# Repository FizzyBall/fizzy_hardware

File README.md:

# Hardware
Embodiment of the robotic ball

<!-- 

Drivetrain V3.0

Drivetrain V3.1

Rigid shell V1

Rigid shell V2

Flexible shell V1

Flexible shell V2
 -->

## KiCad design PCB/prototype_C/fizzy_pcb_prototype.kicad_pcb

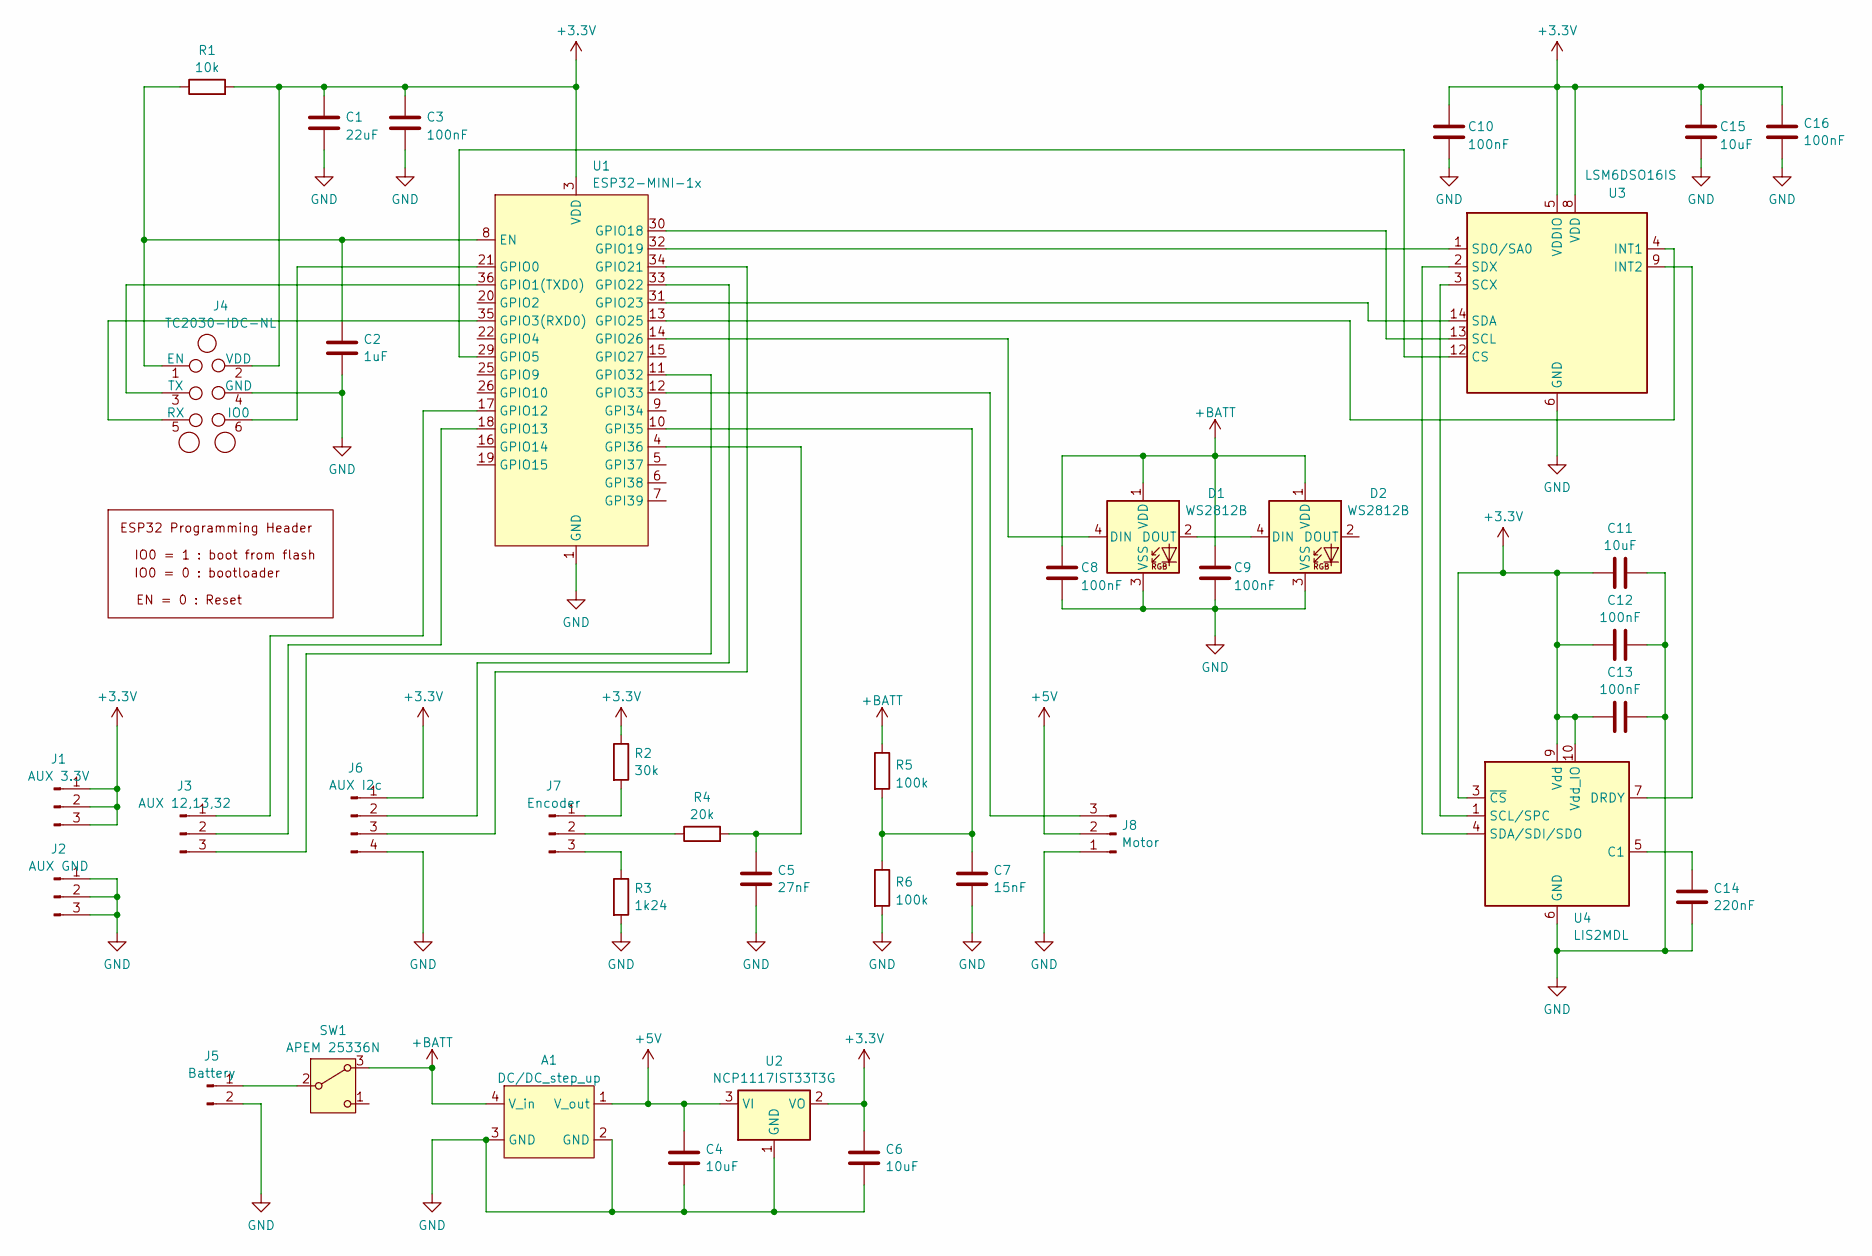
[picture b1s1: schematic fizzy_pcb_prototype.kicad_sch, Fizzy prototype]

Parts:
A1: DC/DC_step_up; DCDC+BAT
C1: 22uF; C_0805_2012Metric
C2: 1uF; C_0603_1608Metric
C3, C8, C9, C10, C12, C13, C16: 100nF; C_0603_1608Metric
C4, C6, C11, C15: 10uF; C_0805_2012Metric
C5: 27nF; C_0603_1608Metric
C7: 15nF; C_0603_1608Metric
C14: 220nF; C_0805_2012Metric
D1, D2: WS2812B; LED_WS2812B_PLCC4_5.0x5.0mm_P3.2mm
J1: AUX 3.3V; PinHeader_1x03_P2.54mm_Vertical
J2: AUX GND; PinHeader_1x03_P2.54mm_Vertical
J3: AUX 12,13,32; PinHeader_1x03_P2.54mm_Vertical
J4: TC2030-IDC_ESP; Tag-Connect_TC2030-IDC-NL_2x03_P1.27mm_Vertical
J5: Battery; BatteryHolder_Keystone_1043_1x18650
J6: AUX I2c; PinHeader_1x04_P2.54mm_Vertical
J7: Encoder; JST_PH_B3B-PH-SM4-TB_1x03-1MP_P2.00mm_Vertical
J8: Motor; JST_PH_B3B-PH-SM4-TB_1x03-1MP_P2.00mm_Vertical
R1: 10k; R_0603_1608Metric
R2: 30k; R_0603_1608Metric
R3: 1k24; R_0603_1608Metric
R4: 20k; R_0603_1608Metric
R5, R6: 100k; R_0603_1608Metric
SW1: APEM 25336N; APEM_25336N
U1: ESP32-MINI-1x; ESP32-MINI-1
U2: NCP1117IST33T3G; SOT-223-3_TabPin2
U3: LSM6DSO16IS; LGA-14_3x2.5mm_P0.5mm_LayoutBorder3x4y
U4: LIS2MDL; LGA-12_2x2mm_P0.5mm

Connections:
+3.3V: C1.2, C3.2, C6.2, C10.2, C11.2, C12.2, C13.2, C15.2, C16.2, J1.1, J1.2, J1.3, J4.2 (VDD), J6.1, R1.2, R2.1, U1.3 (VDD), U2.2 (VO), U3.5 (VDDIO), U3.8 (VDD), U4.3 (~CS), U4.9 (Vdd), U4.10 (Vdd_IO)
+5V: A1.1 (V_out), C4.2, J8.2, U2.3 (VI)
+BATT: A1.4 (V_in), C8.2, C9.2, D1.1 (VDD), D2.1 (VDD), R5.1, SW1.3 (A)
GND: A1.2 (GND), A1.3 (GND), C1.1, C2.2, C3.1, C4.1, C5.1, C6.1, C7.1, C8.1, C9.1, C10.1, C11.1, C12.1, C13.1, C14.1, C15.1, C16.1, D1.3 (VSS), D2.3 (VSS), J2.1, J2.2, J2.3, J4.4 (GND), J5.2, J6.4, J8.1, R3.2, R6.2, U1.1 (GND), U1.2 (GND), U1.27 (GND), U1.38 (GND), U1.39 (GND), U1.40 (GND), U1.41 (GND), U1.42 (GND), U1.43 (GND), U1.44 (GND), U1.45 (GND), U1.46 (GND), U1.47 (GND), U1.48 (GND), U1.49 (GND), U1.50 (GND), U1.51 (GND), U1.52 (GND), U1.53 (GND), U1.54 (GND), U1.55 (GND), U2.1 (GND), U3.6 (GND), U3.7 (GND), U4.6 (GND), U4.8 (GND)
unnamed: D1.4 (DIN), U1.14 (GPIO26)
unnamed: D1.2 (DOUT), D2.4 (DIN)
unnamed: J3.1, U1.17 (GPIO12)
unnamed: J3.2, U1.18 (GPIO13)
unnamed: J3.3, U1.11 (GPIO32)
unnamed: C2.1, J4.1 (EN), R1.1, U1.8 (EN)
unnamed: J4.6 (IO0), U1.21 (GPIO0)
unnamed: J4.5 (RX), U1.35 (GPIO3(RXD0))
unnamed: J4.3 (TX), U1.36 (GPIO1(TXD0))
unnamed: J5.1, SW1.2 (B)
unnamed: J6.2, U1.33 (GPIO22)
unnamed: J6.3, U1.34 (GPIO21)
unnamed: J7.1, R2.2
unnamed: J7.2, R4.1
unnamed: J7.3, R3.1
unnamed: J8.3, U1.12 (GPIO33)
unnamed: C7.2, R5.2, R6.1, U1.10 (GPI35)
unnamed: C5.2, R4.2, U1.4 (GPI36)
unnamed: U1.29 (GPIO5), U3.12 (CS)
unnamed: U1.30 (GPIO18), U3.13 (SCL)
unnamed: U1.32 (GPIO19), U3.1 (SDO/SA0)
unnamed: U1.31 (GPIO23), U3.14 (SDA)
unnamed: U1.13 (GPIO25), U3.4 (INT1)
unnamed: U3.9 (INT2), U4.7 (DRDY)
unnamed: U3.3 (SCX), U4.1 (SCL/SPC)
unnamed: U3.2 (SDX), U4.4 (SDA/SDI/SDO)
unnamed: C14.2, U4.5 (C1)

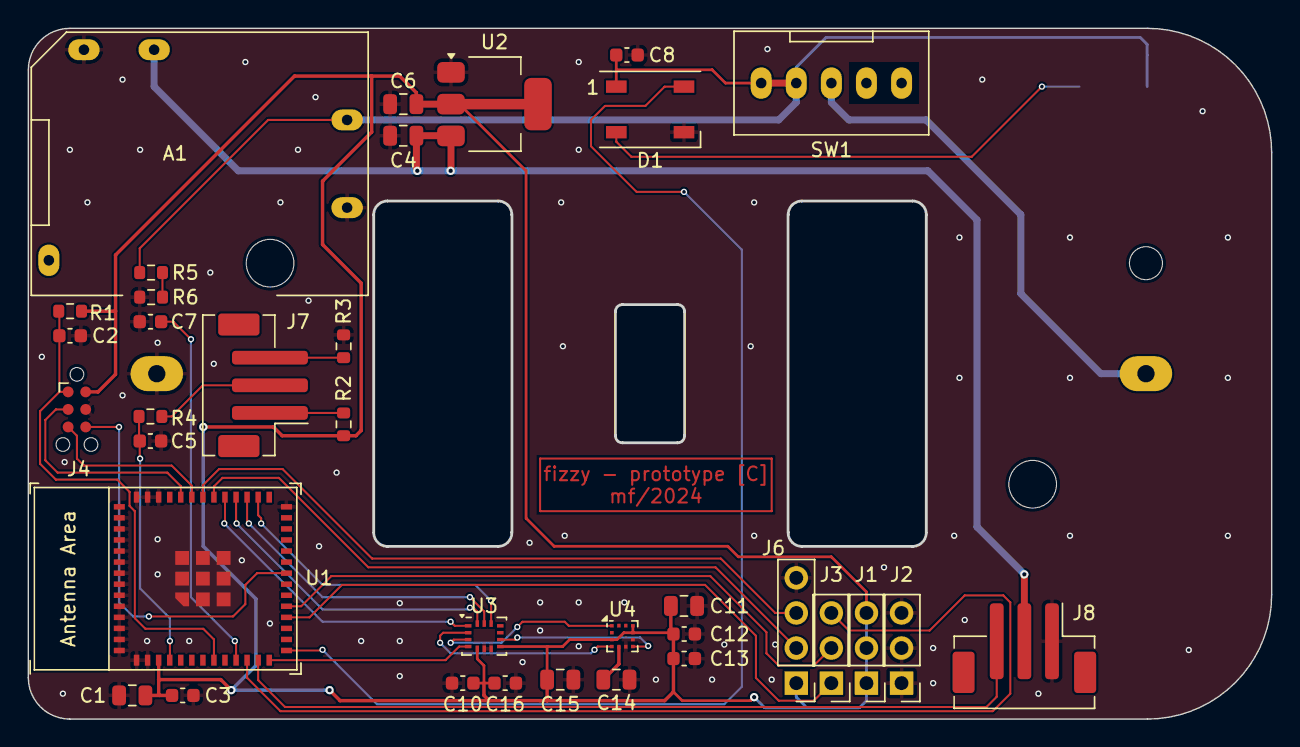
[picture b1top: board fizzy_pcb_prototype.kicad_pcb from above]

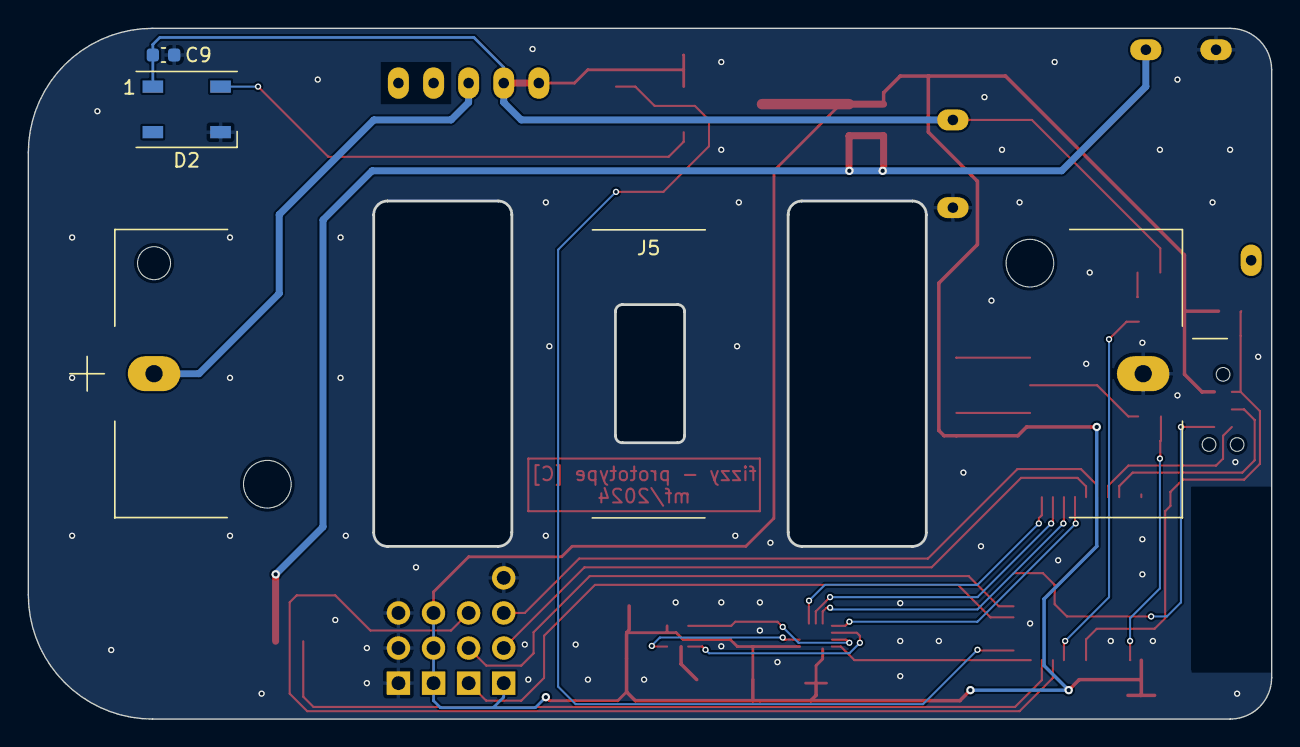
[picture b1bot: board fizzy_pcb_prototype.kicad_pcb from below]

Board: 2 copper layers, 89.9 x 49.9 mm, 38 parts (3 on the bottom side), 31 nets.

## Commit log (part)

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2025-04-25 Create LICENSE
2025-05-12 changed documentation
2025-05-12 modifier change
2025-05-12 added components to the BOM
2025-05-20 changed the length of the drive axis
2025-06-02 commit new BOM list
2025-06-02 readme
2025-09-25 Added picture folder for easy upload to website
2025-09-25 remove image
2025-10-13 changed the location of some printing files for the components + added the assembly step file
2025-10-13 same as previous commit
2025-11-14 added order list as a tab
2026-01-06 fizzy_bom change
2026-01-07 added PCB files for Prototye C
2026-02-27 Create Drivetrain
2026-02-27 Create ignore
2026-02-27 test change
2026-03-04 changed event log
2026-03-04 repo reorg.
